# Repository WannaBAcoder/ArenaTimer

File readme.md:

# ⏱️ Event Match Timer & Lockout System

An open-source, ESP32-based event and match timer platform featuring wireless remote integration, with web interface.

---

## 🚀 Getting Started

### 1. Hardware Orientation & Powering
* **Orientation Flexibility:** The timer can be configured to operate in either horizontal orientation. If your mounting or power cable strategy requires it, you can flip the included hanging bracket to the opposite side and enable **Invert Display** in the web settings to route the power cable from above.
* **Power Requirements:** Connect the timer using the provided power supply. 
> ⚠️ **CRITICAL:** Only use **5V** power supplies capable of delivering at least **60W**. Applying a voltage higher than 5V will **permanently damage** the hardware.

### 2. Initial Wi-Fi & Web UI Setup
1. **Boot Sequence:** Upon power-up, the display initializes with dashes (`--:--`) and the border will blink, indicating it is attempting to connect to the last saved Wi-Fi network.
2. **Access Point (AP) Mode:** If the network is unavailable (or during first-time setup), the timer switches to AP mode, broadcasting its own network:
   * **SSID:** `TimerSetup`
   * **Password:** `12345678`
3. **Connecting to the UI:** * Connect your phone, tablet, or computer to the `TimerSetup` network.
   * Locate the timer's IP address in your device's network connection settings (this process varies by operating system).
   * Open a web browser and enter the IP address to access the control interface.

*Note: The local AP interface is identical to the network interface. If no external Wi-Fi network is available at your venue, you can run the timer in this standalone mode completely offline.*

4. **Station Mode (Optional):** To connect the timer to an existing venue Wi-Fi network, use the configuration section at the bottom of the webpage to save your local **SSID** and **Password**.

---

## ⚙️ Configuration & Features

### 🎮 Wireless Remotes & Pairing
The system supports three battery-powered wireless remotes: **one Main Controller** and **two Driver Ready/Tap-Out buttons** (Red vs. Blue).

* **Pairing Procedure:** Remotes must be paired before deployment. Click **Pair Remote** in the Web UI to enter binding mode, turn on the remote, and press any button. The timer will automatically exit binding mode, and the Web UI status will update to `Paired`.  Repeat independently for each remote.
  * *Pairing Timeout:* Binding mode automatically cancels itself after 15 seconds if no remote responds (with a live countdown shown on screen), rather than hanging indefinitely until a reboot.
* **Driver Ready Lockout:** Enabling the `Require Driver Ready` checkbox prevents a match from starting until both driver remotes register a "Ready" state - the **Start** button itself grays out while waiting, and the ready state for each side is shown directly under the countdown.
  * *Visual Indicators:* The physical white border indicates overall readiness. Individual Red/Blue illumination confirms when each respective driver has ready-ed up.
* **Tap-Out Functionality:** Even if the pre-match lockout is disabled, the driver remotes function by default as tap-out indicators. Pressing them during a match triggers a unique tap-out animation and audio effect (can be toggled off via the checkbox).

### 📻 ESP-NOW and LoRa Remotes, Side by Side
Newer timer boards carry an onboard LoRa radio alongside the original ESP-NOW remote support - both run **at the same time, in the same firmware image**. That means a single timer can have, say, Red paired to an older ESP-NOW remote while Blue and Judge are paired to newer LoRa remotes, so a LoRa-capable board can go into service before every remote in the field is replaced.

* **Per-Role Binding:** Each of Red, Blue, and Judge is paired independently, and the System Status panel shows exactly which radio each one is bound through - `PAIRED (ESP-NOW)`, `PAIRED (LoRa)`, or `PAIRED (LoRa+ESP-NOW)` if the same role has been bound on both.
* **Automatic Hardware Detection:** On boards without the LoRa radio installed, the firmware detects its absence at boot (shown as `LoRa radio: Not detected`) and simply runs ESP-NOW only, rather than wasting startup time retrying a radio that isn't there.

### 🌐 RCE Manager Integration (Experimental, `rce_integration` branch)
The timer can act as a hardware timer for an arena in [RCE Manager](https://www.rcemanager.com): their tablet's Start / Pause / Reset drive the display, and the timer's own controls (web page and Judge remote) drive their clock and stream overlays. Enter the event's integration key and arena name in the new **RCE Manager** box; with nothing entered, the timer behaves exactly as before.

In this mode the 3-2-1 countdown, tapouts, driver-ready, the 2/3-minute switch and Multi-Timer Sync are intentionally switched off, since RCE Manager has no equivalent. It has been tested against a mock of their protocol, **not yet against the real service**. Full instructions, what works, what's disabled and what isn't verified yet: **[Software/RCE_MANAGER.md](Software/RCE_MANAGER.md)**.

### 🔗 Multi-Timer Sync (Web-Based)
Running several mats off one set of remotes already works by pairing the same remote to each timer directly (above) - but for anything triggered from the **web page** (start/pause/reset, time-select, colors, brightness, audio, ready/tapout settings), pair two timers together over WiFi so clicking a button on one applies to both.

* **Setup:** Open the **Multi-Timer Sync** panel, enter the other timer's local IP address (shown on its own page as `My IP`), and click **Sync**. Everything that timer currently has configured pushes over immediately, so both units start in agreement instead of drifting until the next change.
* **What Syncs:** Match control, match time, display color/brightness/flip, audio settings, ready-required, tap-out, and clock mode. Remote button presses are *not* relayed this way - they already reach every timer that remote is directly paired to, with no extra setup needed.
* **One-Directional by Default:** Sync only pushes outward from whichever timer's web page you clicked on - pair both timers to each other's IP if you want either one to be able to drive the other.
* **Naming Timers:** Give each unit a short label (e.g. "Mat 1") at the top of its page - shown in the browser tab too - so it's obvious which page you're looking at when several are open side by side.

### ⏱️ Match Time vs. Set Time
Two different buttons next to the manual MM:SS entry handle two different needs:

* **Set Time:** A one-off override for just the upcoming match. Pressing **Reset** afterward falls back to whatever the standing default already was (the 2/3-minute preset, or a previously-set Match Time).
* **Match Time:** Sets a new standing default - **Reset** keeps returning to this duration until the unit reboots (it isn't saved permanently, so a custom one-off event length doesn't silently become the new default forever). The **Switch 2/3m** button still overrides it either way.

### 🕐 Clock Mode
Toggle **Enable Clock Mode** (in Display Settings) to repurpose the digit display as a wall clock when the timer is idle between matches. The web page itself keeps showing whatever match time was last active (dimmed, since it isn't live) - the physical display is what shows the actual time.

### 🔊 Audio Options
* **Global Toggle:** Easily enable or disable all system audio via the web panel.
* **Output Routing:** Switch between the onboard piezo beeper or a dedicated **relay output** used to switch larger external horn circuits, PA systems, or specialized lighting.
* **Attention Horn:** The Main Controller features a dedicated button to manually trigger the sound effects to grab the attention of competitors or spectators.

### 🔒 Operational Lockout
To prevent accidental mid-match disruption, most configuration options, adjustments, and web buttons are **automatically disabled** while the timer is actively running.

---

## 🛠️ Assembly Process (Electronics Kits)

For users assembling the hardware from the DIY electronics kits, follow this general framework. Refer to the project `BOM.md` for exact hardware sizing, screw counts, and component sourcing links.

### 1. 3D Printed Frame Selection
Choose the frame variant that best fits your 3D printer's build volume:
* **Small Printers:** Cut down to fit standard build plates. Requires more assembly hardware and time but maximizes accessibility.
* **Medium Printers (H2s/H2d Optimized):** A balanced approach featuring lower part counts and optimized print times.
* **Large Printers:** Designed specifically for large-format platforms like the *Elegoo Orange Storm Giga*. 

### 2. Print Settings & Materials
* **Main Frame:** Print in **PETG** for superior mechanical strength and thermal resilience during high-temperature transport or storage.
  * **Walls:** 4–6 perimeters
  * **Infill:** 15–25% Gyroid
* **Lenses:** All frame variations share the same lens files. Print them with enough top/bottom layers to ensure the front face prints **completely solid** to optimize light diffusion and visual clarity.

---

## 🧠 Advanced Development & Limitations

### 📡 RF Limitations & Best Practices
The timer utilizes an **ESP32** module with a printed trace antenna; remotes utilize **ESP8266** modules over ESP-NOW, or on newer timer boards, dedicated **LoRa** radios (see [ESP-NOW and LoRa Remotes, Side by Side](#-esp-now-and-lora-remotes-side-by-side) above) - both with printed antennas.
* **Range & Interference:** While highly reliable in tested arena layouts (e.g., SEMO), performance can degrade at extreme distances or in environments experiencing heavy 2.4 GHz spectrum congestion (crowded Wi-Fi, heavy radio traffic).
* **Upgrades:** If your venue demands extreme range, the hardware can be modified to use variants featuring external SMA antennas. Reach out if you need assistance engineering a solution.
* **Running Multiple Timers:** Pair a single set of remotes to multiple timers by repeating the pairing process on each one (above), and/or bind timers to each other for web-triggered actions - see [Multi-Timer Sync](#-multi-timer-sync-web-based) above.

### 💻 Firmware Upgrades & Exposed I/O
* **Over-The-Air (OTA) Updates:** Firmware updates can be flashed seamlessly without opening the enclosure. Navigate to `http://<your-timer-ip>/update` to access the **ElegantOTA** interface, where you can drag-and-drop compiled `.bin` updates.
* **Restore Factory Settings:** A dedicated button wipes all remotes, WiFi credentials, sync target, and display/audio settings in one step, then reboots - useful for repurposing a unit or ruling out a stale setting during troubleshooting. WiFi credentials alone can also be wiped independently (`Wipe`, next to Save & Reboot) without touching anything else.
* **Hardware Expansion:** Additional I/O pins are deliberately exposed near the internal ESP32 module. Advanced users can open the case and solder directly to these lines to integrate custom addressable LED strips, sensors, or physical inputs.

### ⚡ ESD Precautions & LED Repair
> ⚡ **CAUTION:** The internal PCBs contain components sensitive to Electrostatic Discharge (ESD). Handle bare board assemblies with care during assembly or modifications.

* **Common Failure Mode:** If an ESD event occurs, a single addressable LED in the display chain may burn out. Because the LEDs are wired in series, **if one LED fails, all subsequent data down the chain is blocked**, causing the rest of the display past that point to drop out. 
* **Support:** If you experience an LED failure during assembly or firmware hacking, reach out—these are repairable, and I can guide you through jumping or replacing the compromised pixel. Note that failures have only occurred during loose bench development; fully enclosed units have proven resilient during regular live event usage.

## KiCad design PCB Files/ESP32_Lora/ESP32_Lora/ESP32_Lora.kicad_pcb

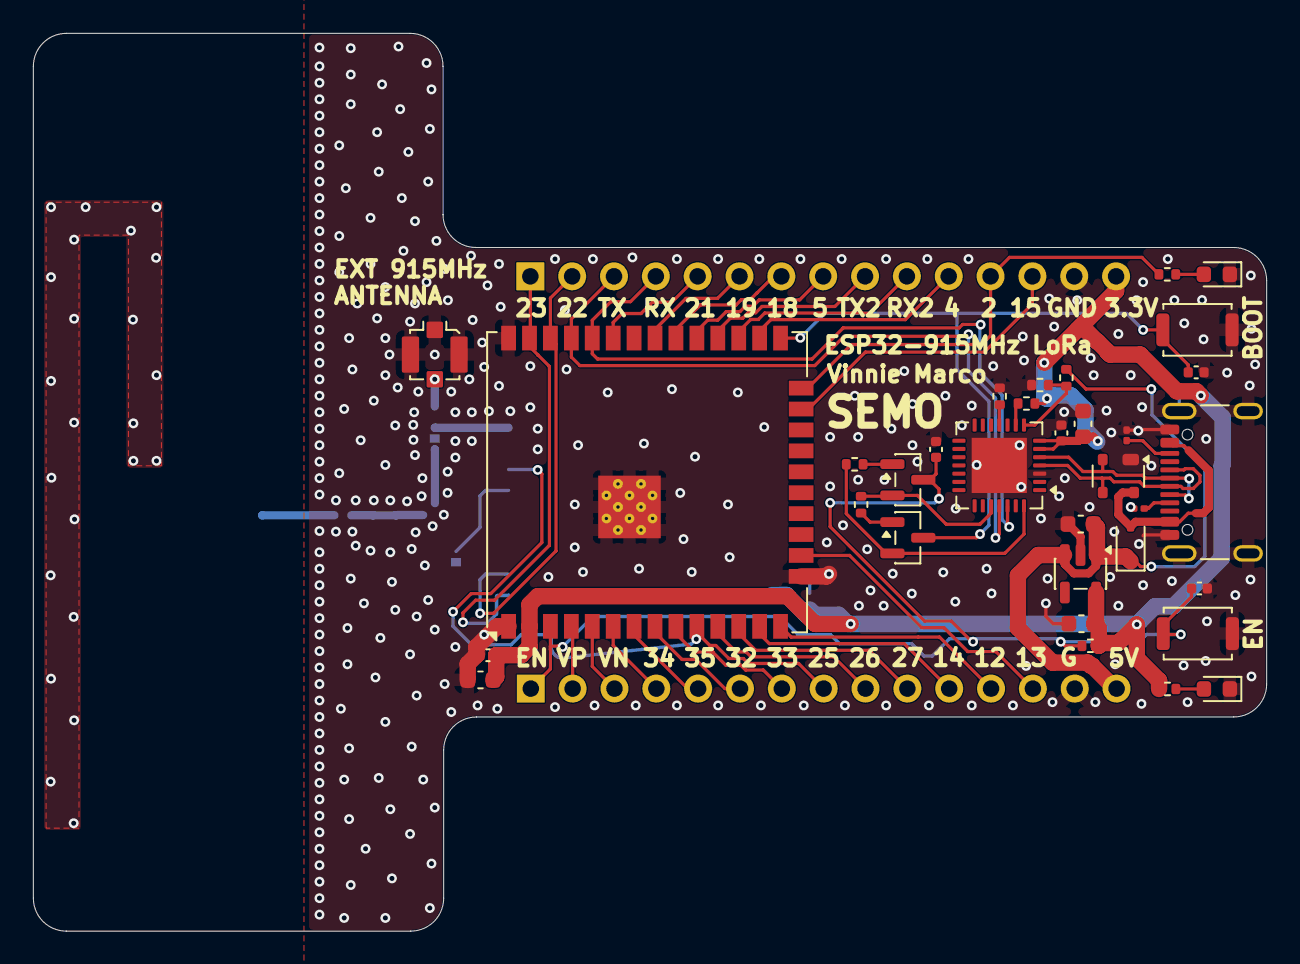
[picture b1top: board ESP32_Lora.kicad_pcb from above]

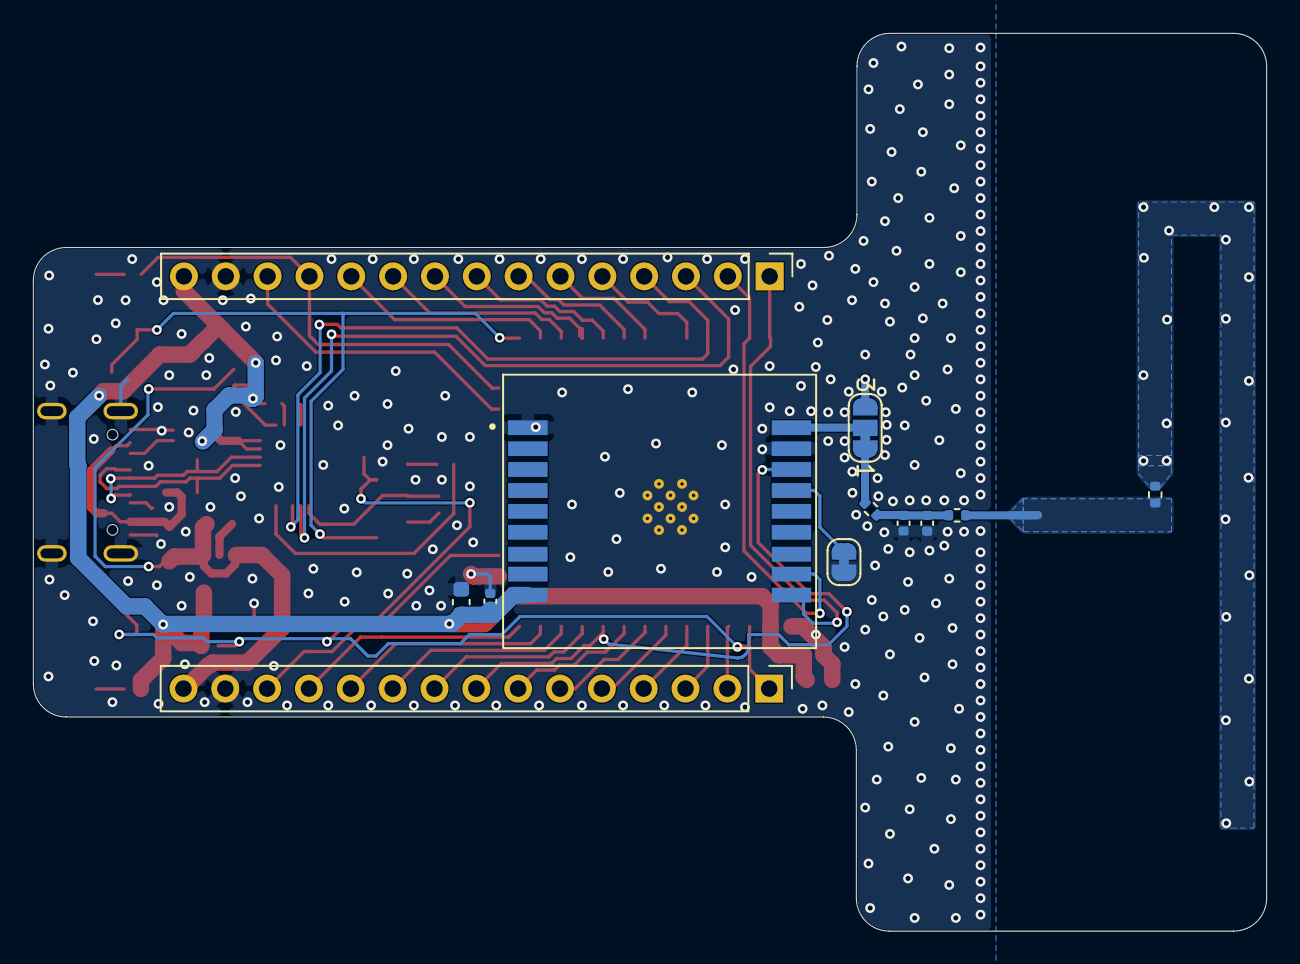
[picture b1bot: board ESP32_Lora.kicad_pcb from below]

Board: 2 copper layers, 74.9 x 54.5 mm, 45 parts (12 on the bottom side), 50 nets.

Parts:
C5, C7, C9, C14, C15: 10uF, 25V; C_0603_1608Metric
C6, C8, C10, C11, C12, C13: 100nF; C_0402_1005Metric
C16: C; C_0402_1005Metric
C17: 4.7pF; C_0402_1005Metric
D1: BAT760-7; D_SOD-323
D10: LED, Red; LED_0603_1608Metric
D12: LED, Blue; LED_0603_1608Metric
J2: Conn_Coaxial_Small; U.FL_Molex_MCRF_73412-0110_Vertical
J15, J16: Conn_01x15_Socket; PinHeader_1x15_P2.54mm_Vertical
J114: USB_C_Receptacle_USB2.0_14P; USB_C_Receptacle_GCT_USB4105-xx-A_16P_TopMnt_Horizontal
JP1: Jumper_2_Bridged; SolderJumper-2_P1.3mm_Bridged_RoundedPad1.0x1.5mm
JP2: SolderJumper_3_Bridged12; SolderJumper-3_P1.3mm_Bridged12_RoundedPad1.0x1.5mm_NumberL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
Q1, Q2: SS8050; SOT-23
R5, R7: 0 ohm; R_0402_1005Metric
R6: 6.2nH; R_0402_1005Metric
R10, R14, R15, R16, R17: 10k; R_0402_1005Metric
R11: 47.5K (1%); R_0402_1005Metric
R12, R18: 470, 1%; R_0402_1005Metric
R13: 22.1K (1%); R_0402_1005Metric
R104, R105: 5.1K; R_0201_0603Metric
SW1, SW2: SW_Push; SW_Push_SPST_NO_Alps_SKRK
U1: Ai-Thinker RA-08H; RA-08H
U3: CP2102N-Axx-xQFN28; QFN-28-1EP_5x5mm_P0.5mm_EP3.35x3.35mm
U4: ESP32-WROOM-32UE
U5: AP2112K-3.3; SOT-23-5
U902: CM1213A−02Sx; SOT-143

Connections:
+3.3V: C5.1, C6.1, C7.1, C8.1, C9.1, C10.1, C15.1, J15.15, R10.1, R12.1, R17.1, U1.9 (VCC), U3.6 (VDD), U3.7 (VREGIN), U4.2 (VDD), U5.5 (VOUT)
+5V: C14.1, D1.1 (K), J16.15, R13.1, U5.1 (VIN), U5.3 (EN)
/2.4GHz: R6.2, R7.1
/BEEPER_EN: J15.7, U4.30 (IO18)
/BORDER_LEDS: J15.9, U4.28 (IO17)
/D2: J15.12, R18.1, U4.24 (IO2)
/D12: J16.12, U4.14 (IO12)
/D26: J16.9, U4.11 (IO26)
/D32: J16.6, U4.8 (IO32)
/D33: J16.7, U4.9 (IO33)
/D34: J16.4, U4.6 (IO34)
/D35: J16.5, U4.7 (IO35)
/DIGIT_LEDS: J15.8, U4.29 (IO5)
/DTR: Q2.2 (E), R15.1, U3.28 (~DTR)
/EN: C11.1, C12.2, J16.1, Q1.3 (C), R17.2, SW1.2, U4.3 (EN)
/IO0: C13.2, Q2.3 (C), SW2.2, U4.25 (IO0)
/MCU_UART0_RX: J15.4, U3.26 (TXD), U4.34 (RXD0/IO3)
/MCU_UART0_TX: J15.3, U3.25 (RXD), U4.35 (TXD0/IO1)
/MCU_UART2_RX: J15.2, U1.11 (TXD/IO17), U4.36 (IO22)
/MCU_UART2_TX: J15.1, U1.10 (LPRXD/IO60), U4.37 (IO23)
/RADIO_RST: J16.8, U1.16 (RST), U4.10 (IO25)
/RELAY_EN: J15.5, U4.33 (IO21)
/RTS: Q1.2 (E), R16.1, U3.24 (~RTS)
/VN: J16.3, U4.5 (SENSOR_VN)
/VP: J16.2, U4.4 (SENSOR_VP)
/nBLUE_RDY_BTN: J15.11, U4.26 (IO4)
/nBUZZER_BTN: J15.6, U4.31 (IO19)
/nPAUSE_BTN: J16.11, U4.13 (IO14)
/nRED_RDY_BTN: J15.10, U4.27 (IO16)
/nRESET_BTN: J15.13, U4.23 (IO15)
/nSTART_BTN: J16.10, U4.12 (IO27)
/nTIME_SEL: J16.13, U4.16 (IO13)
GND: C5.2, C6.2, C7.2, C8.2, C9.2, C10.2, C11.2, C12.1, C13.1, C14.2, C15.2, C16.2, C17.2, D10.1 (K), D12.1 (K), J2.2 (Ext), J15.14, J16.14, J114.A1 (GND), J114.A12 (GND), J114.B1 (GND), J114.B12 (GND), J114.S1 (SHIELD), JP1.1 (A), R11.2, R14.2, R104.2, R105.2, SW1.1, SW2.1, U1.1 (GND), U1.17 (GND), U3.3 (GND), U3.29 (GND), U4.1 (GND), U4.15 (GND), U4.38 (GND), U4.39 (GND), U5.2 (GND), U902.1 (VN)
unnamed: C16.1, C17.1, R5.2, R6.1
unnamed: D1.2 (A), J114.A4 (VBUS), J114.A9 (VBUS), J114.B4 (VBUS), J114.B9 (VBUS), U902.4 (VP)
unnamed: D10.2 (A), R12.2
unnamed: D12.2 (A), R18.2
unnamed: J2.1 (In), JP2.3 (B)
unnamed: J114.A5 (CC1), R104.1
unnamed: J114.B5 (CC2), R105.1
unnamed: JP1.2 (B), U1.15 (IO2/BOOT)
unnamed: JP2.1 (A), R5.1
unnamed: JP2.2 (C), U1.18 (ANT)
unnamed: Q1.1 (B), R15.2
unnamed: Q2.1 (B), R16.2
unnamed: J114.A6 (D+), J114.B6 (D+), U3.4 (D+), U902.3 (CH2)
unnamed: J114.A7 (D-), J114.B7 (D-), U3.5 (D-), U902.2 (CH1)
unnamed: R11.1, R13.2, U3.8 (VBUS)
unnamed: R10.2, U3.9 (~RST)
unnamed: R14.1, U3.11 (~SUSPEND)

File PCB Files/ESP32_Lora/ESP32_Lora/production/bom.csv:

Designator,Footprint,Quantity,Value,LCSC Part #
"C10, C11, C12, C13, C6, C8",0402,6,100nF,C1525
"C14, C15, C5, C7, C9",0603,5,"10uF, 25V",C96446
C16,0402,1,C,DNU
C17,0402,1,4.7pF,C1569
C18,0402,1,2pF,C1558
D1,D_SOD-323,1,BAT760-7,C124187 
D10,0603,1,"LED, Red",C965799
D12,0603,1,"LED, Blue",C965807
J114,USB_C_Receptacle_GCT_USB4105-xx-A_16P_TopMnt_Horizontal,1,USB_C_Receptacle_USB2.0_14P,C309347
"J15, J16",PinHeader_1x15_P2.54mm_Vertical,2,Conn_01x15_Socket,C7501269
J2,U.FL_Molex_MCRF_73412-0110_Vertical,1,Conn_Coaxial_Small,C2987682
JP1,SolderJumper-2_P1.3mm_Bridged_RoundedPad1.0x1.5mm,1,Jumper_2_Bridged,
"Q1, Q2",SOT-23,2,SS8050,C2834467
"R10, R14, R15, R16, R17",0402,5,10k,C25744
"R104, R105",0201,2,5.1K,C367648 
R11,0402,1,47.5K (1%),C2930010 
"R12, R18",0402,2,"470, 1%",C25117 
R13,0402,1,22.1K (1%),C43473
"R5, R6",0402,2,0 ohm,C17168
"SW1, SW2",SW_Push_SPST_NO_Alps_SKRK,2,SW_Push,C115357
U1,RA-08H,1,Ai-Thinker RA-08H,C2991932
U3,QFN-28-1EP_5x5mm_P0.5mm_EP3.35x3.35mm,1,CP2102N-Axx-xQFN28,C964632
U4,ESP32-WROOM-32UE,1,ESP32-WROOM-32UE,C701344
U5,SOT-23-5,1,AP2112K-3.3,C51118
U902,SOT-143,1,CM1213A−02Sx,C19268160

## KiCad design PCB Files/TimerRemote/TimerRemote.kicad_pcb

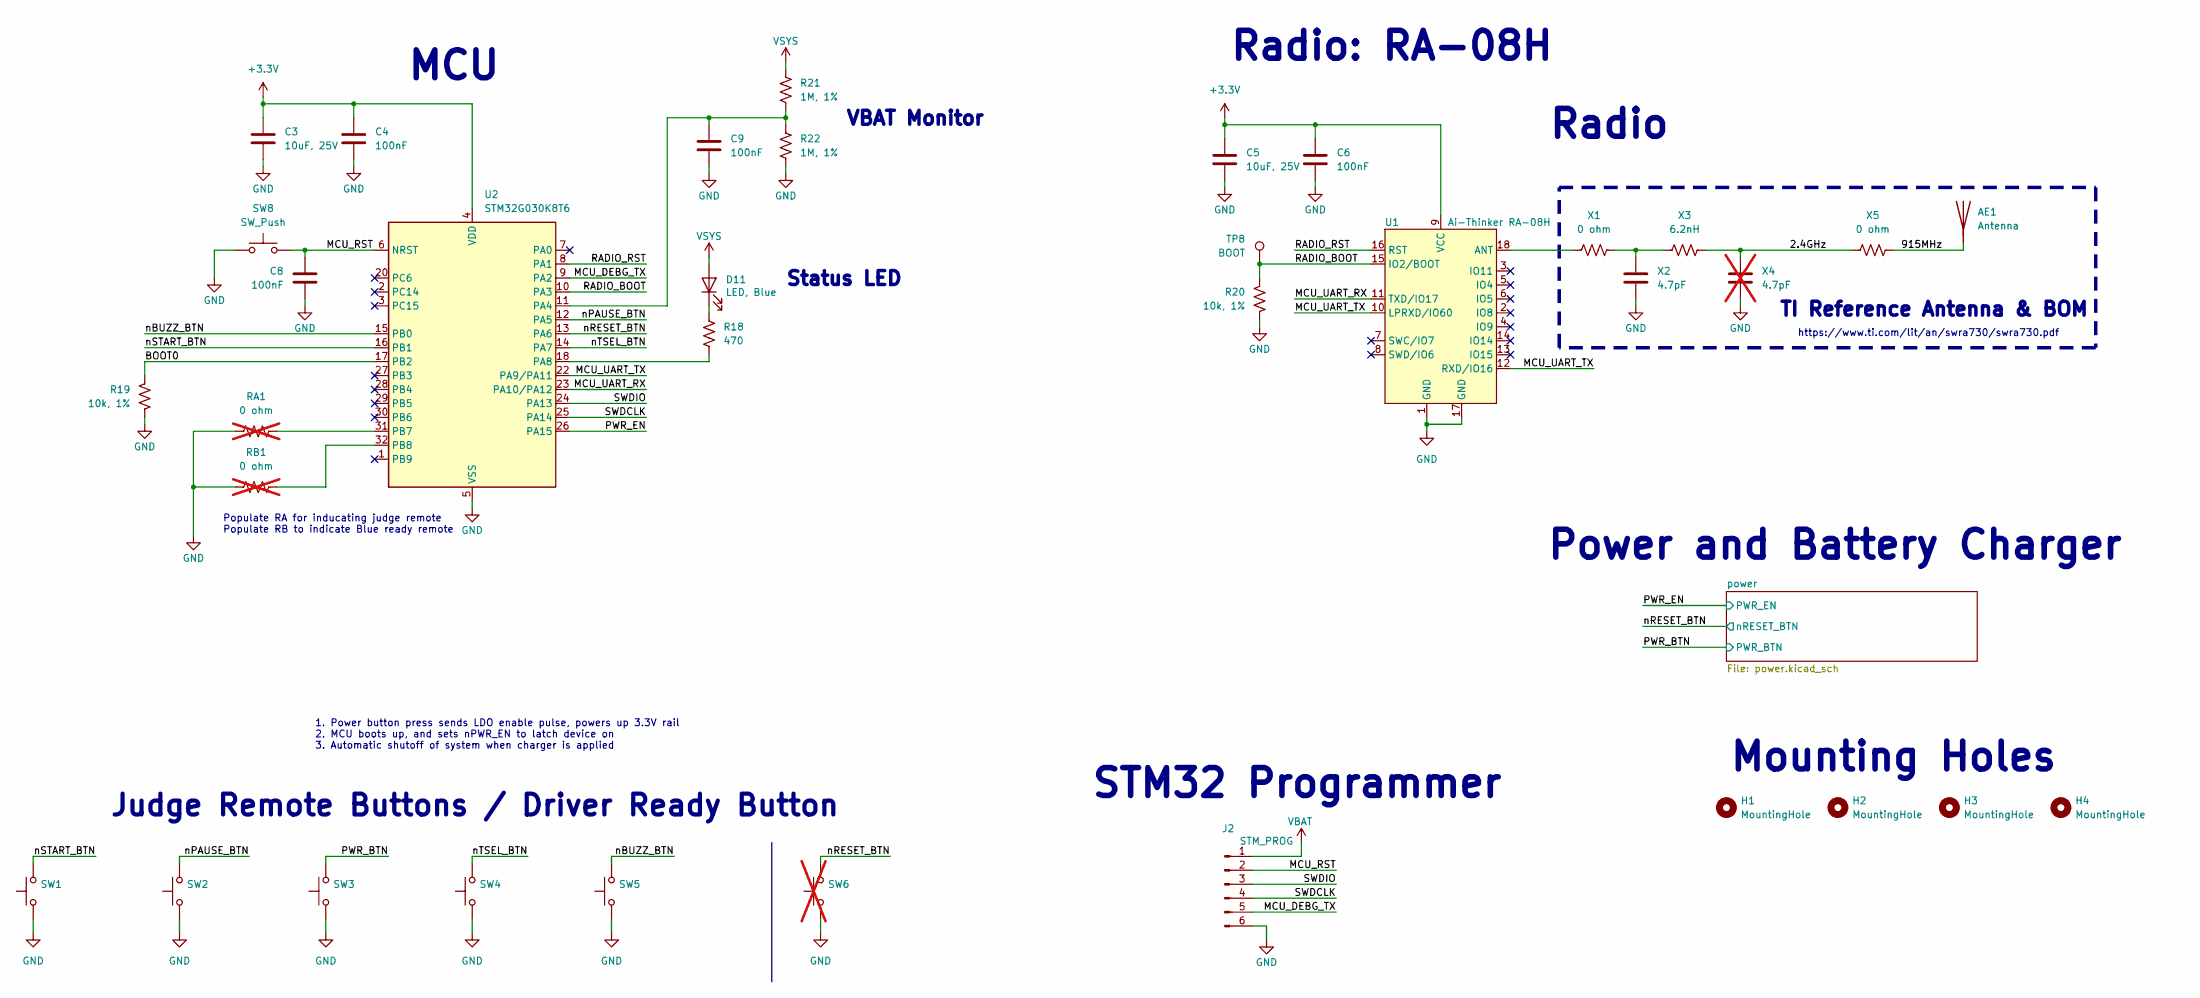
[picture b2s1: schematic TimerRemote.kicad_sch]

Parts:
AE1: Antenna
C3, C5: 10uF, 25V; C_0603_1608Metric; LCSC C96446
C4, C6, C8, C9: 100nF; C_0402_1005Metric; LCSC C1525
D11: LED, Blue; LED_0603_1608Metric; LCSC C965807
H1, H2, H3, H4: MountingHole; MountingHole_3.2mm_M3
J2: STM_PROG; Harwin_M20-89006xx_1x06_P2.54mm_Horizontal; LCSC C20610215
R18: 470; R_0402_1005Metric; LCSC C25117
R19, R20: 10k, 1%; R_0402_1005Metric; LCSC C2906861
R21, R22: 1M, 1%; R_0402_1005Metric; LCSC C26083
RA1: 0 ohm; R_0402_1005Metric; LCSC C17168; not fitted
RB1: 0 ohm; R_0402_1005Metric; LCSC C17168; not fitted
SW1: START; SW_Push_1P1T_NO_CK_PTS125Sx43SMTR; LCSC C18186488
SW2: PAUSE; SW_Push_1P1T_NO_CK_PTS125Sx43SMTR; LCSC C18186488
SW3: RESET; SW_Push_1P1T_NO_CK_PTS125Sx43SMTR; LCSC C18186488
SW4: TIME_SEL; SW_Push_1P1T_NO_CK_PTS125Sx43SMTR; LCSC C18186488
SW5: BUZZER; SW_Push_1P1T_NO_CK_PTS125Sx43SMTR; LCSC C18186488
SW6: BUZZER; SW_Push_1P1T_NO_CK_PTS125Sx43SMTR; LCSC C18186488; not fitted
SW8: SW_Push; SW_Push_1P1T_XKB_TS-1187A; LCSC C318884
TP8: BOOT; TestPoint_Pad_D1.0mm
U1: Ai-Thinker RA-08H; RA-08H; LCSC C2991932
U2: STM32G030K8T6; LQFP-32_7x7mm_P0.8mm; LCSC C431631
X1, X5: 0 ohm; R_0402_1005Metric; LCSC C17168
X2: 4.7pF; C_0402_1005Metric; MPN GJM1555C1H4R7BB01; LCSC C161327
X3: 6.2nH; R_0402_1005Metric; MPN LQ15HN6N2B02; LCSC C7515369
X4: 4.7pF; C_0402_1005Metric; MPN GRM0335C1H4R3CA01; LCSC C1569; not fitted

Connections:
+3.3V: C3.1, C4.1, C5.1, C6.1, U1.9 (VCC), U2.4 (VDD); also elsewhere on the board
/2.4GHz: X3.2, X4.1, X5.1
/915MHz: AE1.1, X5.2
/BOOT0: R19.1, U2.17 (PB2)
/MCU_DEBG_TX: J2.5, U2.9 (PA2)
/MCU_RST: C8.1, J2.2, SW8.2, U2.6 (NRST)
/MCU_UART_RX: U1.11 (TXD/IO17), U2.23 (PA10/PA12)
/MCU_UART_TX: U1.10 (LPRXD/IO60), U1.12 (RXD/IO16), U2.22 (PA9/PA11)
/PWR_BTN: SW3.2; also elsewhere on the board
/PWR_EN: U2.26 (PA15); also elsewhere on the board
/RADIO_BOOT: R20.1, TP8.1 (1_1), U1.15 (IO2/BOOT), U2.10 (PA3)
/RADIO_RST: U1.16 (RST), U2.8 (PA1)
/SWDCLK: J2.4, U2.25 (PA14)
/SWDIO: J2.3, U2.24 (PA13)
/nBUZZ_BTN: SW5.2, U2.15 (PB0)
/nPAUSE_BTN: SW2.2, U2.12 (PA5)
/nRESET_BTN: SW6.2, U2.13 (PA6); also elsewhere on the board
/nSTART_BTN: SW1.2, U2.16 (PB1)
/nTSEL_BTN: SW4.2, U2.14 (PA7)
GND: C3.2, C4.2, C5.2, C6.2, C8.2, C9.2, J2.6, R19.2, R20.2, R22.2, RA1.1, RB1.1, SW1.1, SW2.1, SW3.1, SW4.1, SW5.1, SW6.1, SW8.1, U1.1 (GND), U1.17 (GND), U2.5 (VSS), X2.2, X4.2; also elsewhere on the board
unnamed: D11.1 (K), R18.1
unnamed: U1.18 (ANT), X1.1
unnamed: C9.1, R21.2, R22.1, U2.11 (PA4)
unnamed: R18.2, U2.18 (PA8)
unnamed: RA1.2, U2.31 (PB7)
unnamed: RB1.2, U2.32 (PB8)
unnamed: X1.2, X2.1, X3.1
VBAT: J2.1; also elsewhere on the board
VSYS: D11.2 (A), R21.1; also elsewhere on the board

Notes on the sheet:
1. Power button press sends LDO enable pulse, powers up 3.3V rail 2. MCU boots up, and sets nPWR_EN to latch device on 3. Automatic shutoff of system when charger is applied
STM32 Programmer
Power and Battery Charger
Status LED
https://www.ti.com/lit/an/swra730/swra730.pdf
Judge Remote Buttons / Driver Ready Button
MCU
VBAT Monitor
Radio
TI Reference Antenna & BOM
Mounting Holes
Populate RA for inducating judge remote Populate RB to indicate Blue ready remote
Radio: RA-08H

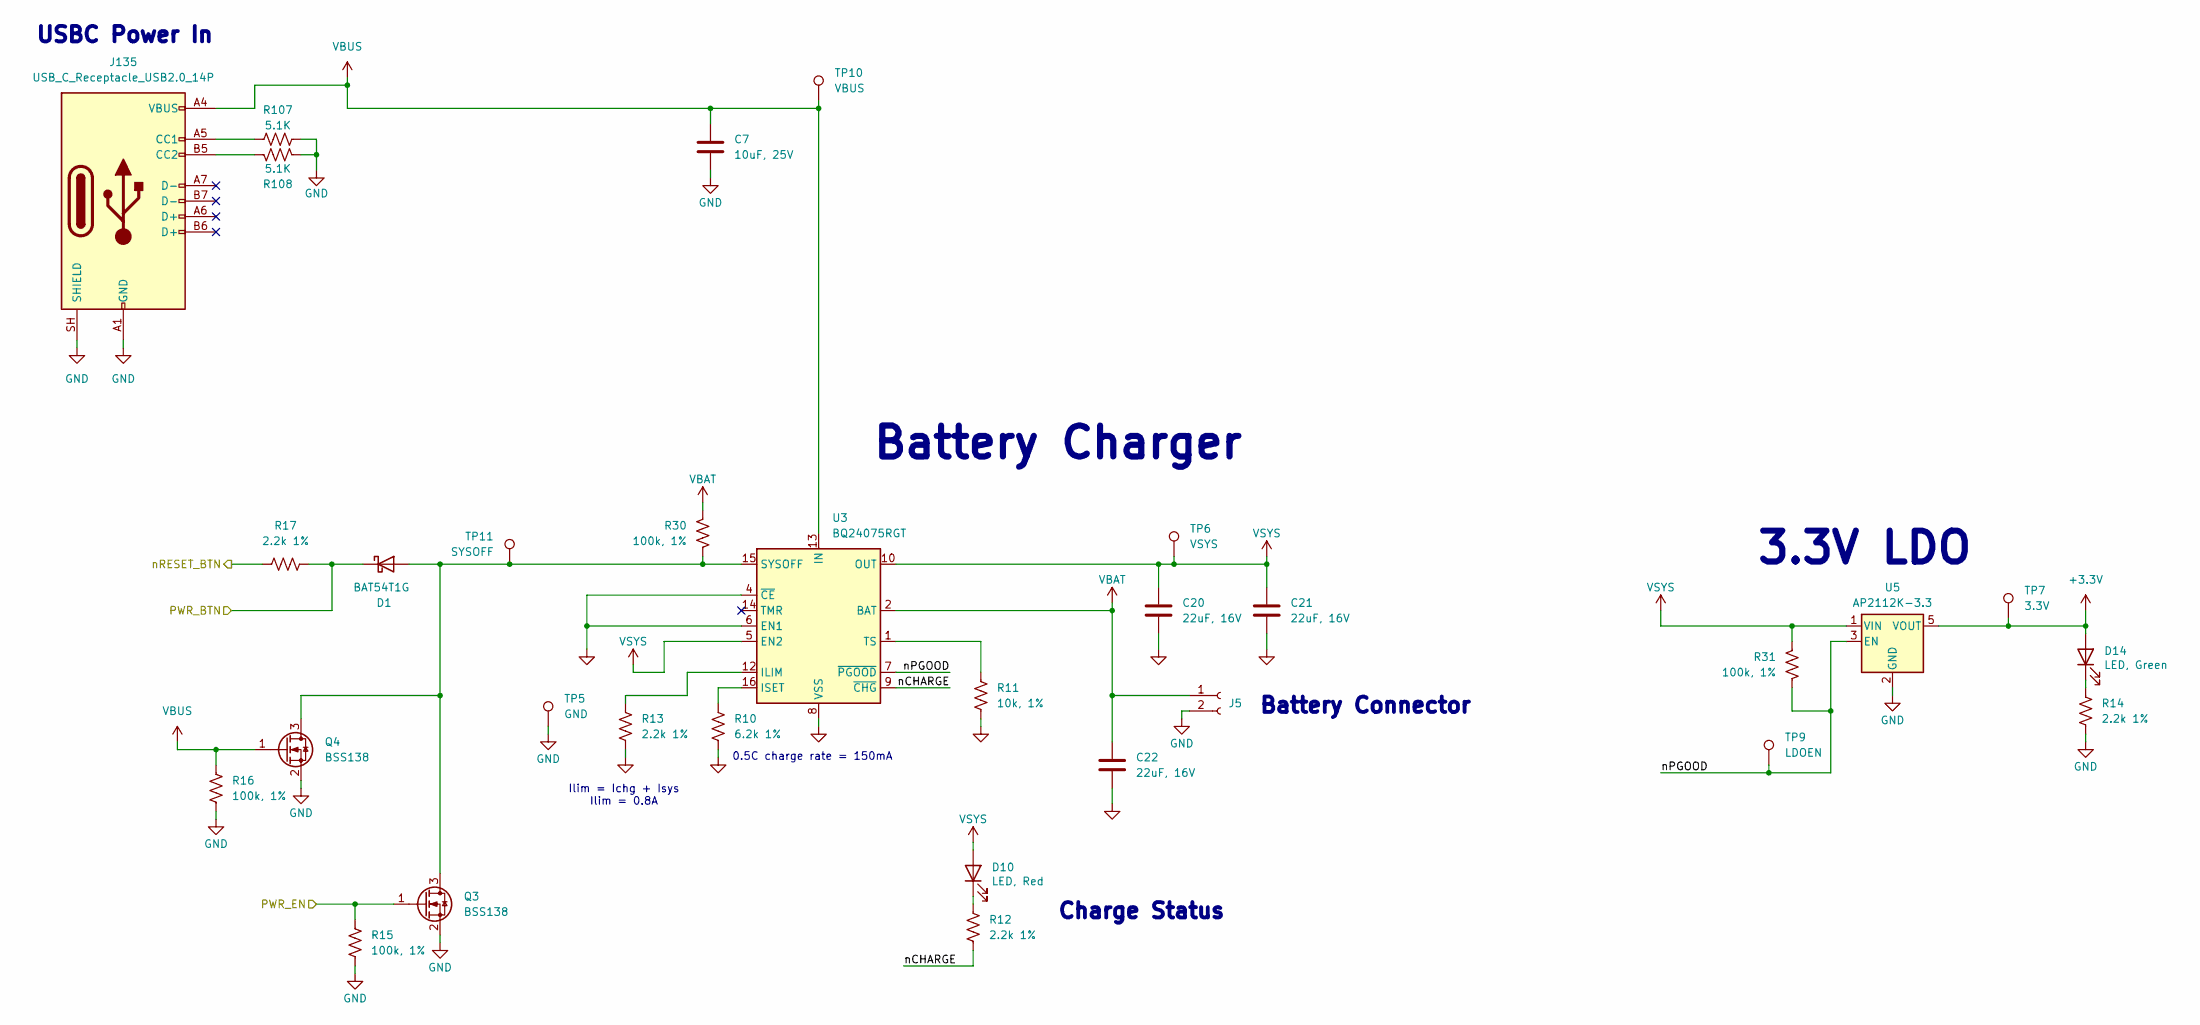
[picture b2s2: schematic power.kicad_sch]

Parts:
C7: 10uF, 25V; C_0603_1608Metric; LCSC C96446
C20, C21, C22: 22uF, 16V; C_0603_1608Metric; LCSC C22367828
D1: BAT54T1G; D_SOD-123; LCSC C152458
D10: LED, Red; LED_0603_1608Metric; LCSC C965799
D14: LED, Green; LED_0603_1608Metric; LCSC C125094
J5: JST_PH_S2B-PH-SM4-TB_1x02-1MP_P2.00mm_Horizontal; LCSC C54582899
J135: USB_C_Receptacle_USB2.0_14P; USB_C_Receptacle_GCT_USB4105-xx-A_16P_TopMnt_Horizontal; LCSC C393939
Q3, Q4: BSS138; SOT-23; LCSC C8490
R10: 6.2k 1%; R_0402_1005Metric; LCSC C25915
R11: 10k, 1%; R_0402_1005Metric; LCSC C2906861
R12, R13, R14, R17: 2.2k 1%; R_0402_1005Metric; LCSC C25879
R15, R16, R30, R31: 100k, 1%; R_0402_1005Metric; LCSC C25741
R107, R108: 5.1K; R_0402_1005Metric; LCSC C25905
TP5: GND; TestPoint_Pad_D1.0mm
TP6: VSYS; TestPoint_Pad_D1.0mm
TP7: 3.3V; TestPoint_Pad_D1.0mm
TP9: LDOEN; TestPoint_Pad_D1.0mm
TP10: VBUS; TestPoint_Pad_D1.0mm
TP11: SYSOFF; TestPoint_Pad_D1.0mm
U3: BQ24075RGT; VQFN-16-1EP_3x3mm_P0.5mm_EP1.6x1.6mm; LCSC C15464
U5: AP2112K-3.3; SOT-23-5; LCSC C51118

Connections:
+3.3V: D14.2 (A), TP7.1 (1_1), U5.5 (VOUT); also elsewhere on the board
/PWR_BTN: D1.1 (K), R17.2; also elsewhere on the board
/PWR_EN: Q3.1 (G), R15.1; also elsewhere on the board
/nRESET_BTN: R17.1; also elsewhere on the board
/power/nCHARGE: R12.2, U3.9 (~CHG)
/power/nPGOOD: R31.2, TP9.1 (1_1), U3.7 (~PGOOD), U5.3 (EN)
GND: C7.2, C20.2, C21.2, C22.2, J5.2, J135.A1 (GND), J135.A12 (GND), J135.B1 (GND), J135.B12 (GND), J135.SH (SHIELD), Q3.2 (S), Q4.2 (S), R10.2, R11.2, R13.2, R14.2, R15.2, R16.2, R107.2, R108.2, TP5.1 (1_1), U3.4 (~CE), U3.6 (EN1), U3.8 (VSS), U3.17 (VSS), U5.2 (GND); also elsewhere on the board
unnamed: D1.2 (A), Q3.3 (D), Q4.3 (D), R30.2, TP11.1 (1_1), U3.15 (SYSOFF)
unnamed: D10.1 (K), R12.1
unnamed: D14.1 (K), R14.1
unnamed: J135.A5 (CC1), R107.1
unnamed: J135.B5 (CC2), R108.1
unnamed: R13.1, U3.12 (ILIM)
unnamed: R10.1, U3.16 (ISET)
unnamed: R11.1, U3.1 (TS)
VBAT: C22.1, J5.1, R30.1, U3.2 (BAT), U3.3 (BAT); also elsewhere on the board
VBUS: C7.1, J135.A4 (VBUS), J135.A9 (VBUS), J135.B4 (VBUS), J135.B9 (VBUS), Q4.1 (G), R16.1, TP10.1 (1_1), U3.13 (IN)
VSYS: C20.1, C21.1, D10.2 (A), R31.1, TP6.1 (1_1), U3.5 (EN2), U3.10 (OUT), U3.11 (OUT), U5.1 (VIN); also elsewhere on the board

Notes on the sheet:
Battery Charger
Battery Connector
3.3V LDO
Ilim = Ichg + Isys Ilim = 0.8A
0.5C charge rate = 150mA
USBC Power In
Charge Status

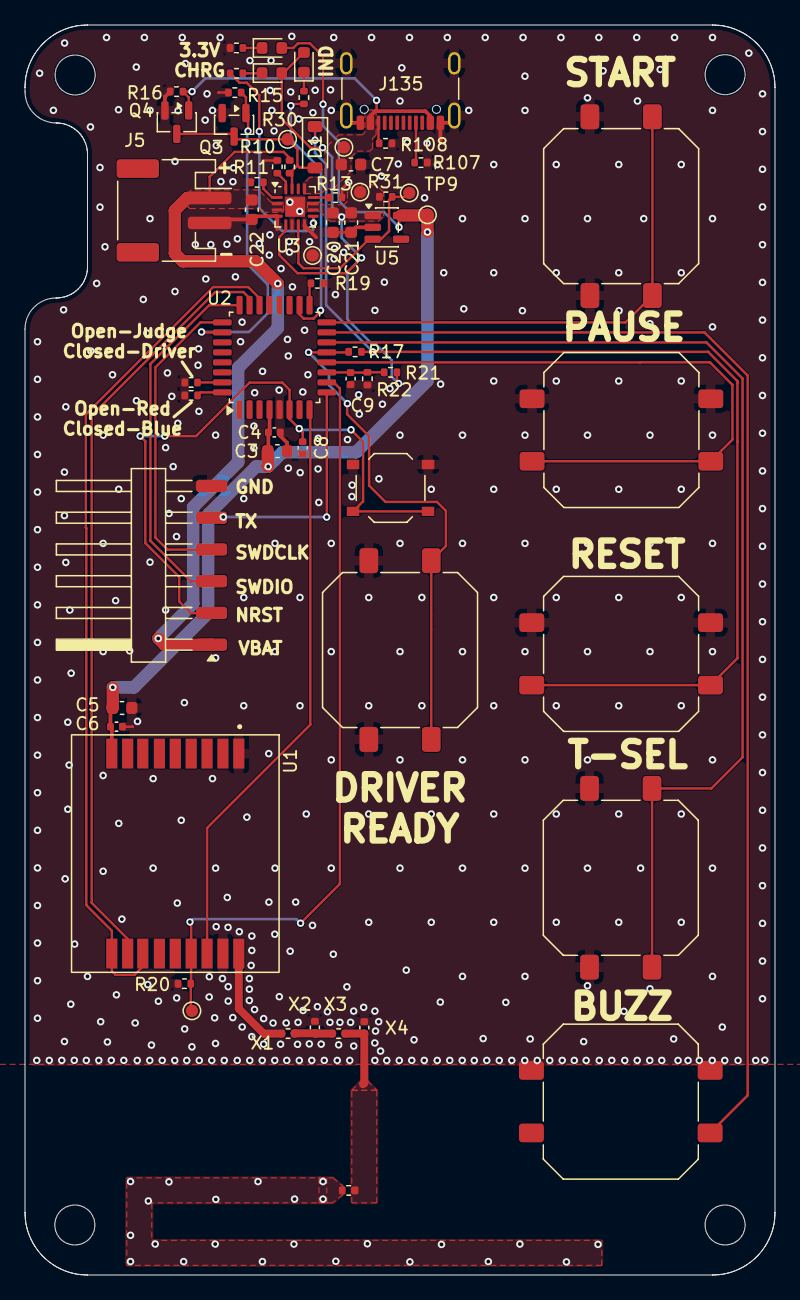
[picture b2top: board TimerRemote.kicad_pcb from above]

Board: 2 copper layers, 60.0 x 100.0 mm, 65 parts (0 on the bottom side), 39 nets.

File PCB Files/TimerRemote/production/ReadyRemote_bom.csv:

Designator,Footprint,Quantity,Value,LCSC Part #
"C20, C21, C22",0603,3,"22uF, 16V",C22367828
"C3, C5, C7",0603,3,"10uF, 25V",C96446
"C4, C6, C8, C9",0402,4,100nF,C1525
D1,D_SOD-123,1,BAT54T1G,C152458
D10,0603,1,"LED, Red",C965799
D11,0603,1,"LED, Blue",C965807
D14,0603,1,"LED, Green",C125094
J135,USB_C_Receptacle_GCT_USB4105-xx-A_16P_TopMnt_Horizontal,1,USB_C_Receptacle_USB2.0_14P,C393939
J2,Harwin_M20-89006xx_1x06_P2.54mm_Horizontal,1,STM_PROG,C20610215
J5,JST_PH_S2B-PH-SM4-TB_1x02-1MP_P2.00mm_Horizontal,1,~,C54582899 
"Q3, Q4",SOT-23,2,BSS138,C8490
R10,0402,1,6.2k 1%,C25915
"R107, R108",0402,2,5.1K,C25905
"R11, R19, R20",0402,3,"10k, 1%",C2906861
"R12, R13, R14, R17",0402,4,2.2k 1%,C25879
"R15, R16, R30, R31",0402,4,"100k, 1%",C25741
R18,0402,1,470,C25117
"R21, R22",0402,2,"1M, 1%",C26083
"RA1, RB1, X1, X5",0402,4,0 ohm,C17168
SW1,SW_Push_1P1T_NO_CK_PTS125Sx43SMTR,1,START,C18186488
SW2,SW_Push_1P1T_NO_CK_PTS125Sx43SMTR,1,PAUSE,C18186488
SW3,SW_Push_1P1T_NO_CK_PTS125Sx43SMTR,1,RESET,C18186488
SW4,SW_Push_1P1T_NO_CK_PTS125Sx43SMTR,1,TIME_SEL,C18186488
"SW5, SW6",SW_Push_1P1T_NO_CK_PTS125Sx43SMTR,2,BUZZER,C18186488
SW8,SW_Push_1P1T_XKB_TS-1187A,1,SW_Push,C318884
U1,RA-08H,1,Ai-Thinker RA-08H,C2991932
U2,LQFP-32_7x7mm_P0.8mm,1,STM32G030K8T6,C431631
U3,VQFN-16-1EP_3x3mm_P0.5mm_EP1.6x1.6mm,1,BQ24075RGT,C15464
U5,SOT-23-5,1,AP2112K-3.3,C51118
X2,0402,1,4.7pF,C161327
X3,0402,1,6.2nH,C7515369
X4,0402,1,4.7pF,C1569

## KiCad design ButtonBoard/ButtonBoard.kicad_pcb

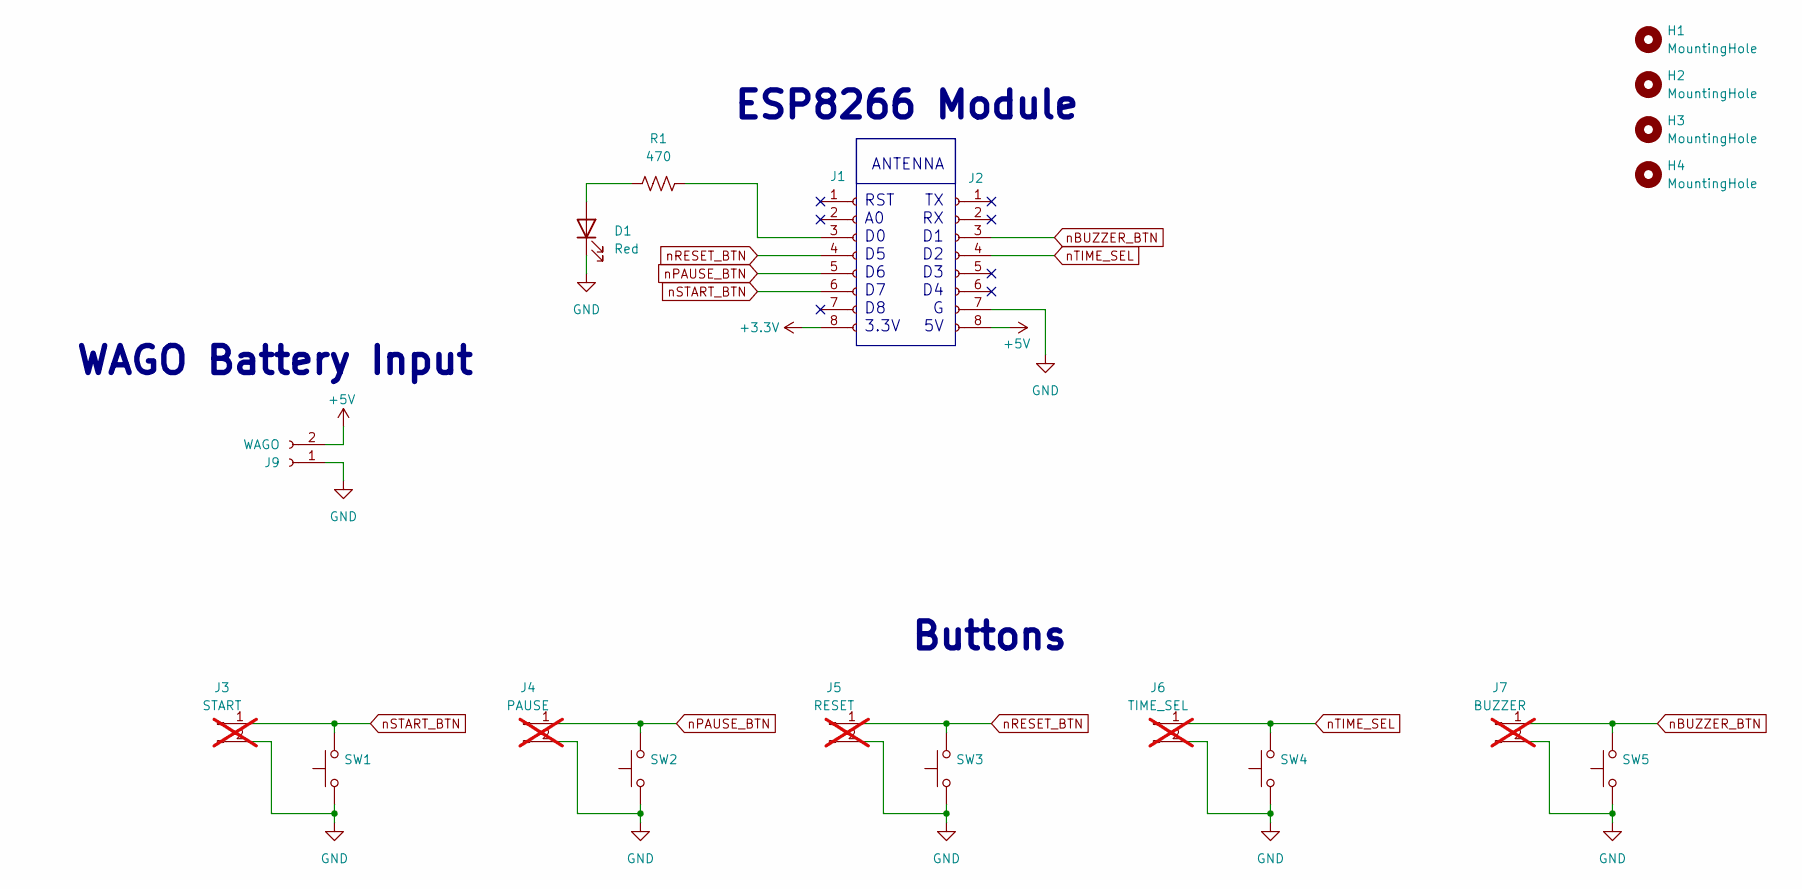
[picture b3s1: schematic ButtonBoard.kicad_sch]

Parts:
D1: Red; LED_0603_1608Metric; LCSC C2286
H1, H2, H3, H4: MountingHole; MountingHole_3.2mm_M3
J1, J2: Conn_01x08_Socket; PinSocket_1x08_P2.54mm_Vertical; LCSC C42431840
J3: START; PinHeader_1x02_P2.54mm_Vertical; not fitted
J4: PAUSE; PinHeader_1x02_P2.54mm_Vertical; not fitted
J5: RESET; PinHeader_1x02_P2.54mm_Vertical; not fitted
J6: TIME_SEL; PinHeader_1x02_P2.54mm_Vertical; not fitted
J7: BUZZER; PinHeader_1x02_P2.54mm_Vertical; not fitted
J9: WAGO; 2060-452_998-404; LCSC C2765055
R1: 470; R_0603_1608Metric; LCSC C23179
SW1: START; SW_PUSH-12mm; LCSC C2888699
SW2: PAUSE; SW_PUSH-12mm; LCSC C2888699
SW3: RESET; SW_PUSH-12mm; LCSC C2888699
SW4: TIME_SEL; SW_PUSH-12mm; LCSC C2888699
SW5: BUZZER; SW_PUSH-12mm; LCSC C2888699

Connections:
+3.3V: J1.8
+5V: J2.8, J9.2
GND: D1.1 (K), J2.7, J3.2, J4.2, J5.2, J6.2, J7.2, J9.1, SW1.1, SW2.1, SW3.1, SW4.1, SW5.1
unnamed: D1.2 (A), R1.1
unnamed: J1.3, R1.2
nBUZZER_BTN: J2.3, J7.1, SW5.2
nPAUSE_BTN: J1.5, J4.1, SW2.2
nRESET_BTN: J1.4, J5.1, SW3.2
nSTART_BTN: J1.6, J3.1, SW1.2
nTIME_SEL: J2.4, J6.1, SW4.2

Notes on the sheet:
ESP8266 Module
Buttons
RST A0 D0 D5 D6 D7 D8 3.3V
WAGO Battery Input
ANTENNA
TX RX D1 D2 D3 D4 G 5V
